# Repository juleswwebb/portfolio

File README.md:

# Jules Webb — Engineering Portfolio

A static engineering portfolio for **https://juleswwebb.github.io/portfolio/**.

The site includes an editorial homepage, four standalone project case studies,
an interactive subsystem viewer, project filters, image detail dialogs, responsive
navigation and social sharing metadata. It uses plain HTML, CSS and JavaScript,
with locally hosted images and no runtime dependencies, trackers or external fonts.

## Preview

```bash
python3 -m http.server 4173
```

Open http://localhost:4173. Run `python3 verify.py` to check local links, fragment
targets, images, headings and metadata. Run `node --check app.js` for JavaScript
syntax validation.

## Deploy

In this repository’s **Settings → Pages → Build and deployment**, select
**GitHub Actions** as the source. The workflow in `.github/workflows/pages.yml`
validates and deploys the public site files after a push to `main`. It can also
be run manually from the Actions tab.

Only the HTML pages, CSS, JavaScript, assets and crawler files are included in
the deployed artifact. The source does not contain the LinkedIn PDF, coursework
reports, firmware, engineering source repositories or private recordings.

## Update

- Edit `index.html` for the introduction, experience, contact links and project cards.
- Edit each project’s HTML for its case study and credits.
- Edit `styles.css` for the design; `app.js` controls progressive enhancements.
- Put optimised project images in `assets/`; update alt text and captions too.
- Update canonical URLs, `sitemap.xml`, `robots.txt`, the social-image URL and
  `404.html` if the repository name or hosting domain changes.

## Content provenance

Professional information and the LinkedIn URL were taken from the user-supplied
LinkedIn profile export dated 7 October 2026. No private analytics or unrelated
profile recommendations were used.

- **Line follower:** Group 13 project report, design figures and application images.
  Team members and reported results are credited in the case study.
- **RoboDev:** collaborative repository documentation and a 3D render made from
  its current KiCad signals board. Planned specifications are identified as such;
  the visualisation does not imply fabricated or validated hardware.
- **RoboCup:** project firmware/tooling documentation and an Arena View screenshot.
  Ongoing hardware validation and dead-reckoning limitations are stated.
- **Frame solver:** application documentation and generated analysis figures.
  Historical reference checks are described as documented development history.

Confirm specific individual contributions before changing the team descriptions
to first-person ownership claims. Update development status as projects progress.

## Interactive browser edition

Seven case studies now include the elevator PLC, CNC mechanical design and ENCE361 step counter. `structure-lab.html` runs a JavaScript port of the original Python direct-stiffness engine in a module worker. It supports axial trusses, Euler–Bernoulli / Timoshenko frames, end releases, rotated supports, nodal and member loads, drawing/editing, undo/redo, JSON sessions, force diagrams and worked matrix downloads. Internal units are SI; UI conversions are explicit. Deformation uses finite-element interpolation, and stress output is axial stress (bending and buckling checks are not included).

`node tests/fea-engine.test.mjs` checks analytical mechanics, stability failures, constrained-load reactions and frozen results generated from the original Python `frame_toolkit.Structure`. The Pages workflow runs these checks alongside the static-site verifier.

`design-library.html` uses a self-hosted Apache-licensed model-viewer (license included) to render actual GLB geometry. Models load on selection; rendered PCB views use optimized WebP previews and downloadable full PNGs. Camera presets, orbit/zoom, auto-rotation, studio background and view export are available. Download packs include actual available source CAD and renders. All original project workspaces remain untouched.

The shared Group 13 OneDrive folder contains files that are cloud placeholders and could not be opened during this export. Affected native archives are marked partial, omit unavailable files and contain `FILES-AWAITING-ONEDRIVE-SYNC.txt`. `assets/models/source-inventory.json` records inclusion status. Supplied STL/3MF exports provide mechanical browser geometry; SolidWorks source parts/assemblies remain native downloads. 3MF placements are print layouts, not reconstructed robot assemblies. Component-library STEP references are identified separately from custom PCB designs.

The elevator, CNC and step-counter web demos are labelled recreations/illustrations. They do not execute the physical controller firmware or claim measured hardware performance. Actual CNC and step-counter project photography is pending.

Motion uses native CSS, SVG and canvas, pauses expensive loops offscreen and honours reduced-motion preferences. No analytics or account/login is required. Locally saved structural models remain in the visitor's browser.

PCB GLB materials use the green default soldermask seen in the KiCad rendered previews. CAD geometry is retained; component materials are adjusted for readable browser lighting. Source STEP and KiCad exports remain available.

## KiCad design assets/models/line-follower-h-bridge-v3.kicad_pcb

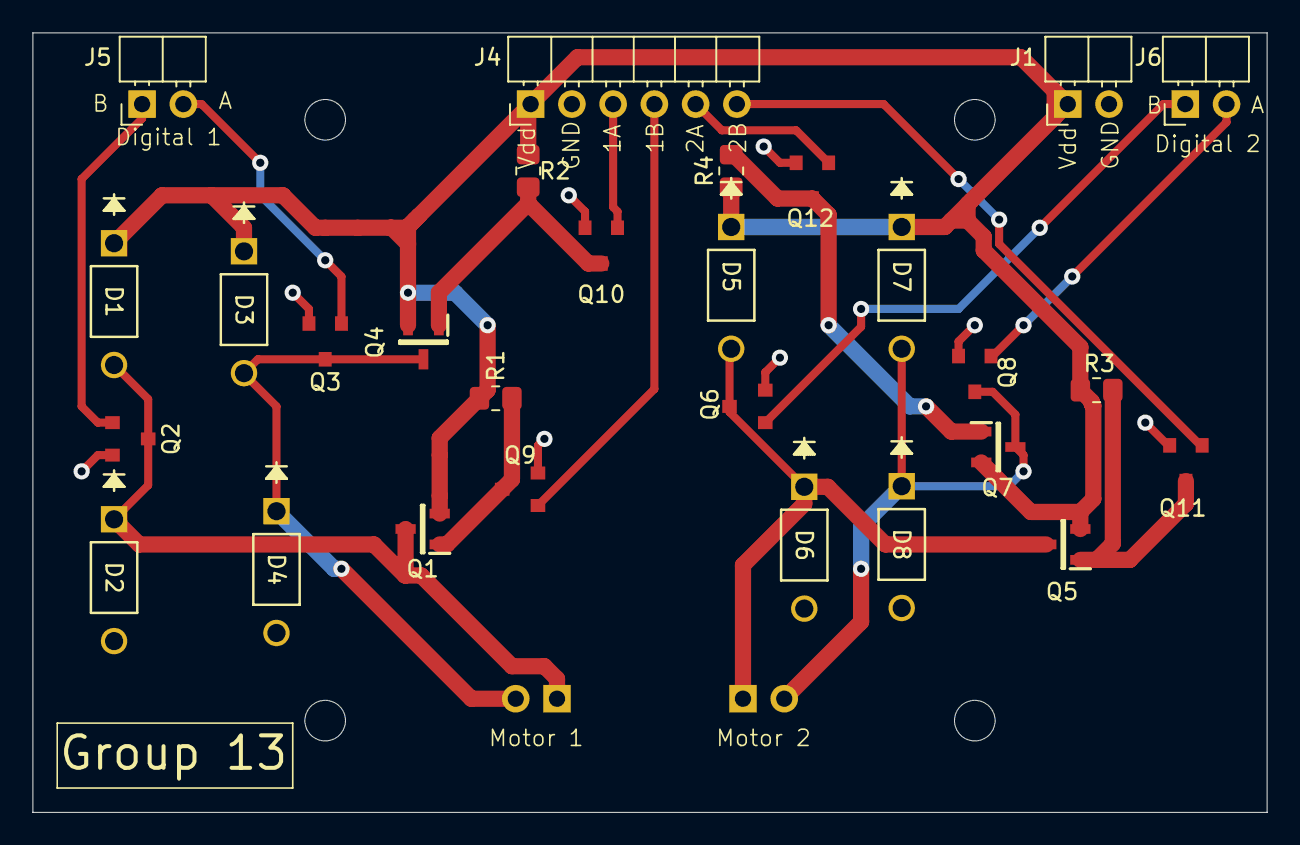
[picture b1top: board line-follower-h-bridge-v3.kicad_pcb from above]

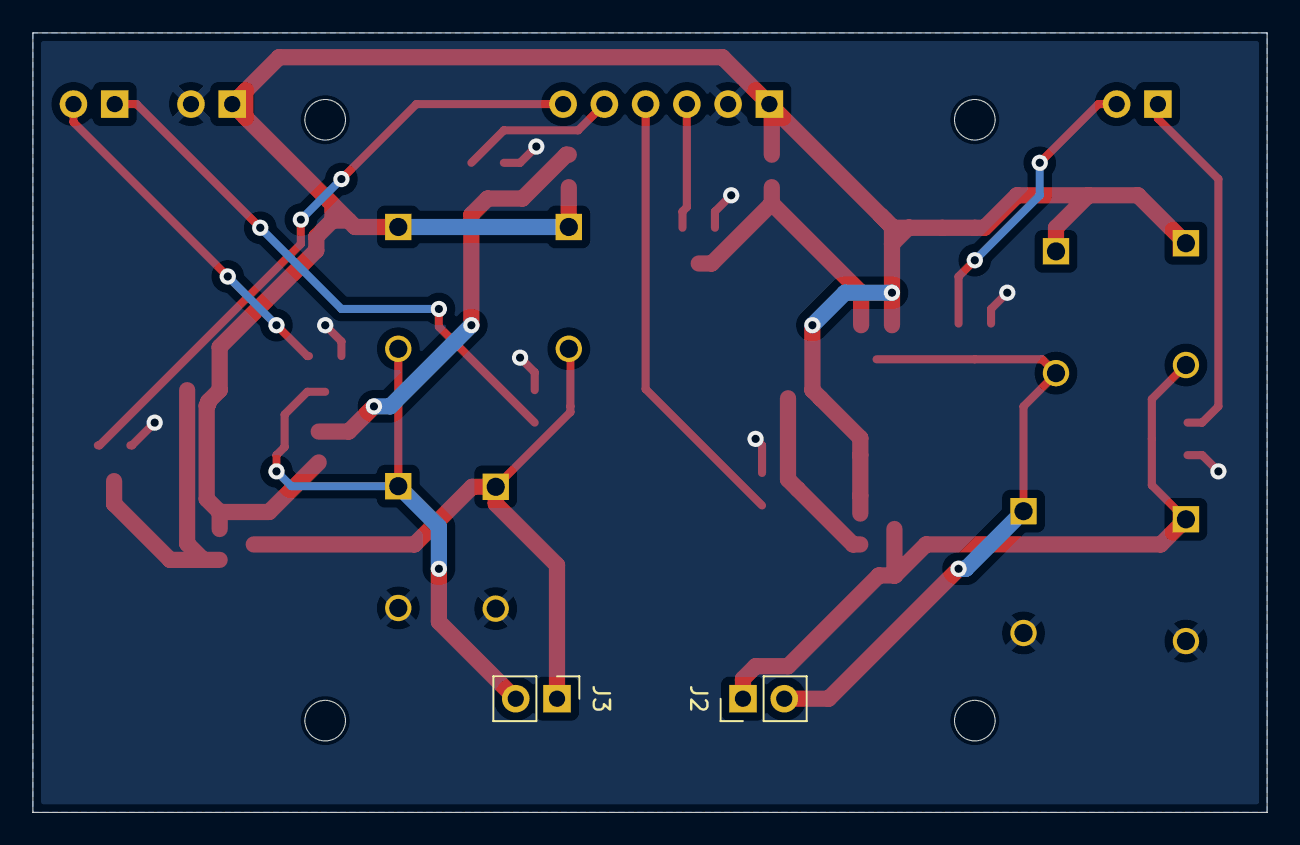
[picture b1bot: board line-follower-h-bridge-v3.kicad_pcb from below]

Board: 2 copper layers, 76.0 x 48.0 mm, 34 parts (2 on the bottom side), 18 nets.

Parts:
D1, D2, D3, D4, D5, D6, D7, D8: D; DO-41_DIO
H1, H2, H3, H4: MountingHole; MountingHole_2.5mm
J1: Battery; PinHeader_1x02_P2.54mm_Horizontal
J2: Motor 1; PinHeader_1x02_P2.54mm_Vertical
J3: Motor 2; PinHeader_1x02_P2.54mm_Vertical
J4: Conn_01x06; PinHeader_1x06_P2.54mm_Horizontal
J5, J6: Conn_01x02; PinHeader_1x02_P2.54mm_Horizontal
Q1, Q4, Q5, Q7: SI2333DDS-T1-GE3; SOT95P237X112-3N
Q2, Q3, Q6, Q8, Q9, Q10, Q11, Q12: BSR802NL6327HTSA1; TRANS_BC846B_215
R1, R2, R3, R4: 10k; R_0805_2012Metric_Pad1.20x1.40mm_HandSolder

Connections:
Dig1A: J5.2, Q3.1 (G)
Dig1B: J5.1, Q2.1 (G)
Dig2A: J6.2, Q8.1 (G)
Dig2B: J6.1, Q6.1 (G)
GND: D2.2 (A), D4.2 (A), D6.2 (A), D8.2 (A), J1.2, J4.2, Q2.2 (S), Q3.2 (S), Q6.2 (S), Q8.2 (S), Q9.2 (S), Q10.2 (S), Q11.2 (S), Q12.2 (S)
unnamed: D1.2 (A), D2.1 (K), J2.1, Q1.3, Q2.3 (D)
unnamed: D3.2 (A), D4.1 (K), J2.2, Q3.3 (D), Q4.3
unnamed: D5.2 (A), D6.1 (K), J3.1, Q5.3, Q6.3 (D)
unnamed: D7.2 (A), D8.1 (K), J3.2, Q7.3, Q8.3 (D)
unnamed: Q1.1, Q9.3 (D), R1.2
unnamed: Q4.1, Q10.3 (D), R2.2
unnamed: Q5.1, Q11.3 (D), R3.2
unnamed: Q7.1, Q12.3 (D), R4.2
PWM1A: J4.3, Q10.1 (G)
PWM1B: J4.4, Q9.1 (G)
PWM2A: J4.5, Q12.1 (G)
PWM2B: J4.6, Q11.1 (G)
Vdd: D1.1 (K), D3.1 (K), D5.1 (K), D7.1 (K), J1.1, J4.1, Q1.2, Q4.2, Q5.2, Q7.2, R1.1, R2.1, R3.1, R4.1

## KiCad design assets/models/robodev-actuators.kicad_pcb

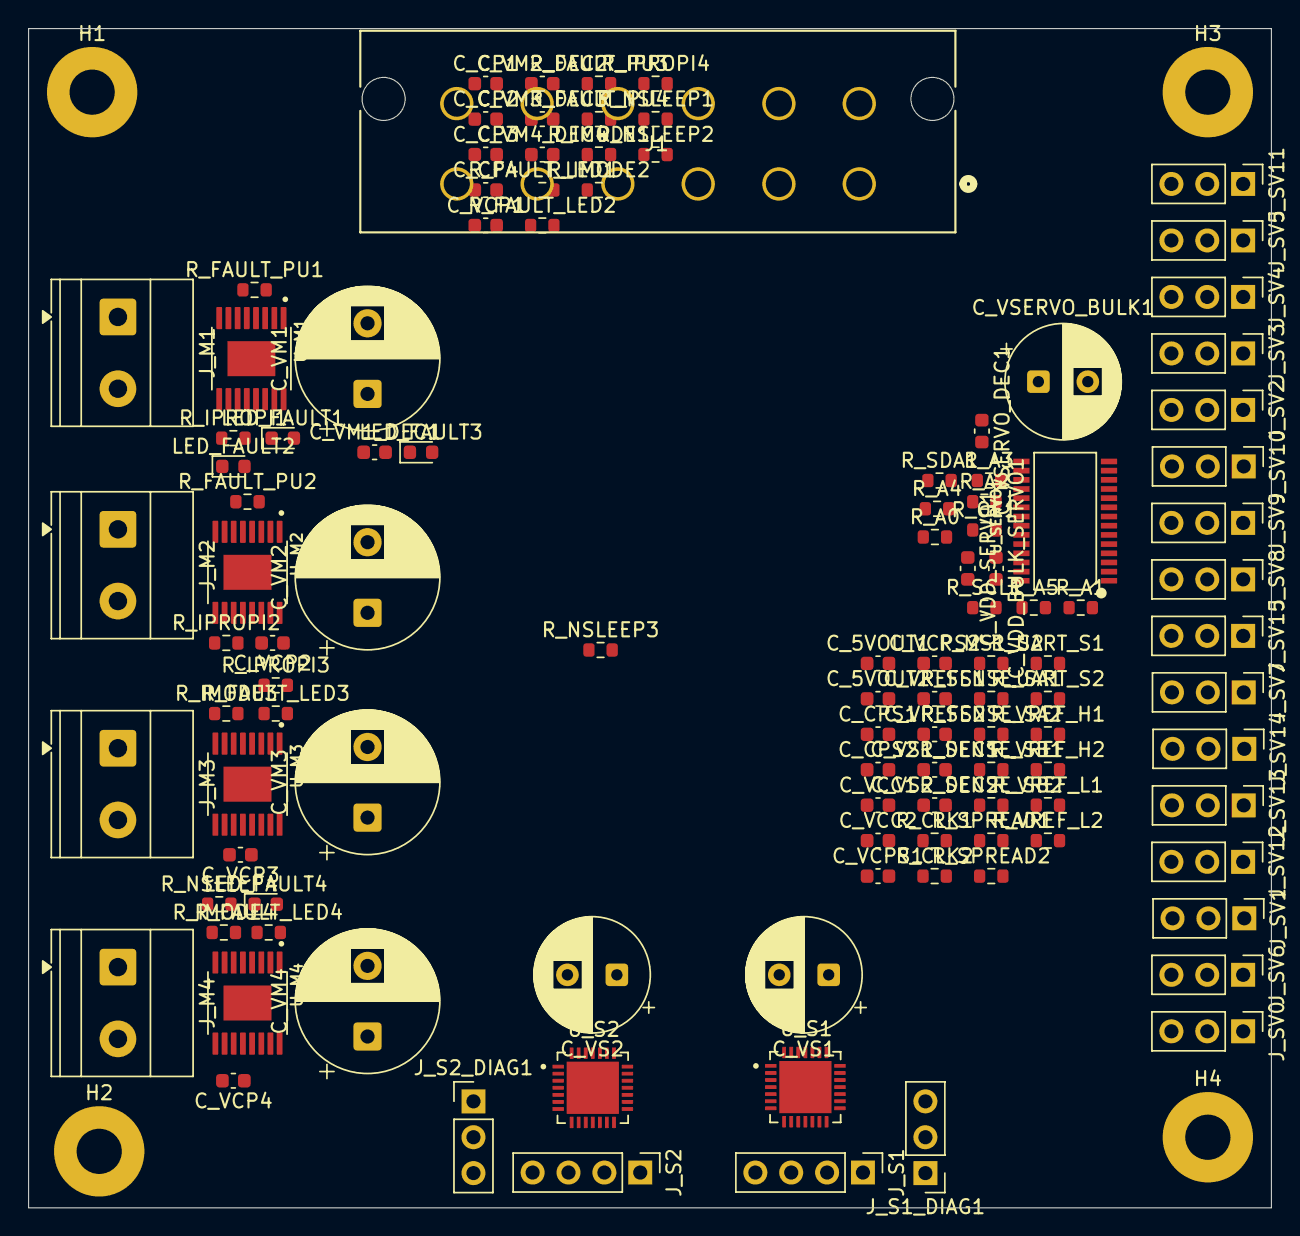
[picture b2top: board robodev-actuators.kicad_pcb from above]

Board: 4 copper layers, 88.0 x 83.5 mm, 118 parts (0 on the bottom side), 113 nets, no tracks yet.

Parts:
C_5VOUT1, C_5VOUT2: 4.7 µF 10V X5R; C_0603_1608Metric
C_CP1: 22nF 50V X7R; C_0603_1608Metric
C_CP2, C_CP3, C_CP4: 22 nF 50V X7R; C_0603_1608Metric
C_CPS1, C_CPS2: 100 nF 50V X7R; C_0603_1608Metric
C_VCC1, C_VCC2: 100 nF 10V X7R; C_0603_1608Metric
C_VCP1, C_VCP2, C_VCP3, C_VCP4: 100 nF 50V X7R; C_0603_1608Metric
C_VCPS1, C_VCPS2: 100 nF 50V X7R; C_0603_1608Metric
C_VDD_BULK_SERVO1: 10 µF 10V X5R; C_0603_1608Metric
C_VDD_SERVO1: 100 nF 10V X7R; C_0603_1608Metric
C_VM1, C_VM2, C_VM3, C_VM4: 470 µF 50V electrolytic; CP_Radial_D10.0mm_P5.00mm
C_VM1_DEC1, C_VM2_DEC2, C_VM3_DEC3, C_VM4_DEC4: 100 nF 50V X7R; C_0603_1608Metric
C_VREFS1, C_VREFS2: 100 nF 10V X7R; C_0603_1608Metric
C_VS1, C_VS2: 100 µF 50V electrolytic; CP_Radial_D8.0mm_P3.50mm
C_VS1_DEC1, C_VS2_DEC2: 100 nF 50V X7R; C_0603_1608Metric
C_VSERVO_BULK1: 220 µF 25V electrolytic; CP_Radial_D8.0mm_P3.50mm
C_VSERVO_DEC1: 100 nF 50V X7R; C_0603_1608Metric
H1, H2, H3, H4: MountingHole_Pad; MountingHole_3.2mm_M3_Pad
J1: 768290012; CONN_SD-76829-0100_12_MOL
J_M1, J_M2, J_M3, J_M4: Conn_01x02; TerminalBlock_Phoenix_MKDS-1,5-2-5.08_1x02_P5.08mm_Horizont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
J_S1, J_S2: Stepper 4-pin 2.54mm; PinHeader_1x04_P2.54mm_Vertical
J_S1_DIAG1: Stepper 1 DIAG/INDEX; PinHeader_1x03_P2.54mm_Vertical
J_S2_DIAG1: Stepper 2 DIAG/INDEX; PinHeader_1x03_P2.54mm_Vertical
J_SV0, J_SV1, J_SV2, J_SV3, J_SV4, J_SV5, J_SV6, J_SV7, J_SV8, J_SV9, J_SV10, J_SV11, J_SV12, J_SV13, J_SV14, J_SV15: Conn_01x03; PinHeader_1x03_P2.54mm_Vertical
LED_FAULT1, LED_FAULT2, LED_FAULT3, LED_FAULT4: LTST-C190KRKT Red; LED_0603_1608Metric
R_A0, R_A1, R_A2, R_A3, R_A4, R_A5: 100 kΩ 1% 0603; R_0603_1608Metric
R_CLK1, R_CLK2: 100 kΩ 1% 0603; R_0603_1608Metric
R_FAULT_LED1, R_FAULT_LED2, R_FAULT_LED3, R_FAULT_LED4: 1 kΩ 1% 0603; R_0603_1608Metric
R_FAULT_PU1, R_FAULT_PU2, R_FAULT_PU3, R_FAULT_PU4: 10 kΩ 1% 0603; R_0603_1608Metric
R_IMODE1, R_IMODE2, R_IMODE3, R_IMODE4: 20 kΩ 1% 0603; R_0603_1608Metric
R_IPROPI1, R_IPROPI2, R_IPROPI3, R_IPROPI4: 1 kΩ 1% 0603; R_0603_1608Metric
R_MS1_S2: 10 kΩ 1% 0603; R_0603_1608Metric
R_NSLEEP1, R_NSLEEP2, R_NSLEEP3, R_NSLEEP4: 100 kΩ 1% 0603; R_0603_1608Metric
R_OE1: 100 kΩ 1% 0603; R_0603_1608Metric
R_SCL1: 4.7 kΩ 1% 0603; R_0603_1608Metric
R_SDA1: 4.7 kΩ 1% 0603; R_0603_1608Metric
R_SENSE_SA1, R_SENSE_SA2: 100 mΩ 1% 0603; R_0603_1608Metric
R_SENSE_SB1, R_SENSE_SB2: 100 mΩ 1% 0603; R_0603_1608Metric
R_SPREAD1, R_SPREAD2: 100 kΩ 1% 0603; R_0603_1608Metric
R_UART_S1, R_UART_S2: 1 kΩ 1% 0603; R_0603_1608Metric
R_VREF_H1, R_VREF_H2: 10 kΩ 1% 0603; R_0603_1608Metric
R_VREF_L1, R_VREF_L2: 27 kΩ 1% 0603; R_0603_1608Metric
U_M1, U_M2, U_M3, U_M4: DRV8874PWPR; SOP65P640X120-17N
U_S1, U_S2: TMC2209-LA-T; QFN50P500X500X90-29N
U_SERVO1: PCA9685PW; TSSOP28-0.65-9.7X4.4MM

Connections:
+3V3: C_VCC1.2, C_VCC2.2, C_VDD_BULK_SERVO1.2, C_VDD_SERVO1.2, R_FAULT_PU1.1, R_FAULT_PU2.1, R_FAULT_PU3.1, R_FAULT_PU4.1, R_MS1_S2.1, R_NSLEEP1.1, R_NSLEEP2.1, R_NSLEEP3.1, R_NSLEEP4.1, R_SCL1.1, R_SDA1.1, R_VREF_H1.1, R_VREF_H2.1, U_M1.5 (VREF), U_M2.5 (VREF), U_M3.5 (VREF), U_M4.5 (VREF), U_S1.15 (VCC_IO), U_S2.15 (VCC_IO), U_SERVO1.28 (VDD)
/MGND: J1.7, J1.8
/SERVOGND: J1.11, J1.12
/STEPGND: J1.9, J1.10
/V_MOT: J1.3, J1.4
/V_SERVO: J1.1, J1.2
/V_STEP: J1.5, J1.6
/motor_dc/IPROPI_M1: R_IPROPI1.1, U_M1.6 (IPROPI)
/motor_dc/IPROPI_M2: R_IPROPI2.1, U_M2.6 (IPROPI)
/motor_dc/IPROPI_M3: R_IPROPI3.1, U_M3.6 (IPROPI)
/motor_dc/IPROPI_M4: R_IPROPI4.1, U_M4.6 (IPROPI)
/motor_dc/VMOT: C_VCP1.2, C_VCP2.2, C_VCP3.2, C_VCP4.2, C_VM1.1, C_VM1_DEC1.1, C_VM2.1, C_VM2_DEC2.1, C_VM3.1, C_VM3_DEC3.1, C_VM4.1, C_VM4_DEC4.1, U_M1.11 (VM), U_M2.11 (VM), U_M3.11 (VM), U_M4.11 (VM)
/motor_servo/I2C_SCL: R_SCL1.2, U_SERVO1.26 (SCL)
/motor_servo/I2C_SDA: R_SDA1.2, U_SERVO1.27 (SDA)
/motor_servo/SV_PWM0: J_SV0.3, U_SERVO1.6 (LED0)
/motor_servo/SV_PWM1: J_SV1.3, U_SERVO1.7 (LED1)
/motor_servo/SV_PWM2: J_SV2.3, U_SERVO1.8 (LED2)
/motor_servo/SV_PWM3: J_SV3.3, U_SERVO1.9 (LED3)
/motor_servo/SV_PWM4: J_SV4.3, U_SERVO1.10 (LED4)
/motor_servo/SV_PWM5: J_SV5.3, U_SERVO1.11 (LED5)
/motor_servo/SV_PWM6: J_SV6.3, U_SERVO1.12 (LED6)
/motor_servo/SV_PWM7: J_SV7.3, U_SERVO1.13 (LED7)
/motor_servo/SV_PWM8: J_SV8.3, U_SERVO1.15 (LED8)
/motor_servo/SV_PWM9: J_SV9.3, U_SERVO1.16 (LED9)
/motor_servo/SV_PWM10: J_SV10.3, U_SERVO1.17 (LED10)
/motor_servo/SV_PWM11: J_SV11.3, U_SERVO1.18 (LED11)
/motor_servo/SV_PWM12: J_SV12.3, U_SERVO1.19 (LED12)
/motor_servo/SV_PWM13: J_SV13.3, U_SERVO1.20 (LED13)
/motor_servo/SV_PWM14: J_SV14.3, U_SERVO1.21 (LED14)
/motor_servo/SV_PWM15: J_SV15.3, U_SERVO1.22 (LED15)
/motor_stepper/S1_VREF: C_VREFS1.1, R_VREF_H1.2, R_VREF_L1.1, U_S1.17 (VREF)
/motor_stepper/S2_VREF: C_VREFS2.1, R_VREF_H2.2, R_VREF_L2.1, U_S2.17 (VREF)
/motor_stepper/TMC_UART: R_UART_S1.1, R_UART_S2.1
GND: C_5VOUT1.2, C_5VOUT2.2, C_VCC1.1, C_VCC2.1, C_VDD_BULK_SERVO1.1, C_VDD_SERVO1.1, C_VM1.2, C_VM1_DEC1.2, C_VM2.2, C_VM2_DEC2.2, C_VM3.2, C_VM3_DEC3.2, C_VM4.2, C_VM4_DEC4.2, C_VREFS1.2, C_VREFS2.2, H1.1, H2.1, H3.1, H4.1, J_S1_DIAG1.1, J_S2_DIAG1.1, LED_FAULT1.1 (K), LED_FAULT2.1 (K), LED_FAULT3.1 (K), LED_FAULT4.1 (K), R_A0.1, R_A1.1, R_A2.1, R_A3.1, R_A4.1, R_A5.1, R_CLK1.1, R_CLK2.1, R_IMODE1.1, R_IMODE2.1, R_IMODE3.1, R_IMODE4.1, R_IPROPI1.2, R_IPROPI2.2, R_IPROPI3.2, R_IPROPI4.2, R_OE1.1, R_SPREAD1.1, R_SPREAD2.1, R_VREF_L1.2, R_VREF_L2.2, U_M1.16 (PMODE), U_M2.16 (PMODE), U_M3.16 (PMODE), U_M4.16 (PMODE), U_S1.9 (MS1_AD0), U_S1.10 (MS2_AD1), U_S2.10 (MS2_AD1), U_SERVO1.14 (VSS), U_SERVO1.25 (EXTCLK)
MGND: U_M1.9 (PGND), U_M1.15 (GND), U_M2.9 (PGND), U_M2.15 (GND), U_M3.9 (PGND), U_M3.15 (GND), U_M4.9 (PGND), U_M4.15 (GND)
unnamed: J_M1.1, U_M1.8 (OUT1)
unnamed: J_M1.2, U_M1.10 (OUT2)
unnamed: J_M2.1, U_M2.8 (OUT1)
unnamed: J_M2.2, U_M2.10 (OUT2)
unnamed: J_M3.1, U_M3.8 (OUT1)
unnamed: J_M3.2, U_M3.10 (OUT2)
unnamed: J_M4.1, U_M4.8 (OUT1)
unnamed: J_M4.2, U_M4.10 (OUT2)
unnamed: J_S1.1, U_S1.24 (OA1)
unnamed: J_S1.2, U_S1.21 (OA2)
unnamed: J_S1.3, U_S1.26 (OB1)
unnamed: J_S1.4, U_S1.1 (OB2)
unnamed: J_S1_DIAG1.2, U_S1.11 (DIAG)
unnamed: J_S1_DIAG1.3, U_S1.12 (INDEX)
unnamed: J_S2.1, U_S2.24 (OA1)
unnamed: J_S2.2, U_S2.21 (OA2)
unnamed: J_S2.3, U_S2.26 (OB1)
unnamed: J_S2.4, U_S2.1 (OB2)
unnamed: J_S2_DIAG1.2, U_S2.11 (DIAG)
unnamed: J_S2_DIAG1.3, U_S2.12 (INDEX)
unnamed: LED_FAULT1.2 (A), R_FAULT_LED1.2
unnamed: LED_FAULT2.2 (A), R_FAULT_LED2.2
unnamed: LED_FAULT3.2 (A), R_FAULT_LED3.2
unnamed: LED_FAULT4.2 (A), R_FAULT_LED4.2
unnamed: C_CP1.1, U_M1.13 (CPH)
unnamed: C_CP1.2, U_M1.14 (CPL)
unnamed: R_IMODE1.2, U_M1.7 (IMODE)
unnamed: R_FAULT_LED1.1, R_FAULT_PU1.2, U_M1.4 (NFAULT)
unnamed: R_NSLEEP1.2, U_M1.3 (NSLEEP)
unnamed: C_VCP1.1, U_M1.12 (VCP)
unnamed: C_CP2.1, U_M2.13 (CPH)
unnamed: C_CP2.2, U_M2.14 (CPL)
unnamed: R_IMODE2.2, U_M2.7 (IMODE)
unnamed: R_FAULT_LED2.1, R_FAULT_PU2.2, U_M2.4 (NFAULT)
unnamed: R_NSLEEP2.2, U_M2.3 (NSLEEP)
unnamed: C_VCP2.1, U_M2.12 (VCP)
unnamed: C_CP3.1, U_M3.13 (CPH)
unnamed: C_CP3.2, U_M3.14 (CPL)
unnamed: R_IMODE3.2, U_M3.7 (IMODE)
unnamed: R_FAULT_LED3.1, R_FAULT_PU3.2, U_M3.4 (NFAULT)
unnamed: R_NSLEEP3.2, U_M3.3 (NSLEEP)
unnamed: C_VCP3.1, U_M3.12 (VCP)
unnamed: C_CP4.1, U_M4.13 (CPH)
unnamed: C_CP4.2, U_M4.14 (CPL)
unnamed: R_IMODE4.2, U_M4.7 (IMODE)
unnamed: R_FAULT_LED4.1, R_FAULT_PU4.2, U_M4.4 (NFAULT)
unnamed: R_NSLEEP4.2, U_M4.3 (NSLEEP)
unnamed: C_VCP4.1, U_M4.12 (VCP)
unnamed: C_5VOUT1.1, U_S1.8 (5VOUT)
unnamed: R_SENSE_SA1.1, U_S1.23 (BRA)
unnamed: R_SENSE_SB1.1, U_S1.27 (BRB)
unnamed: R_CLK1.2, U_S1.13 (CLK)
unnamed: C_CPS1.1, U_S1.5 (CPI)
unnamed: C_CPS1.2, U_S1.4 (CPO)
unnamed: R_SPREAD1.2, U_S1.7 (SPREAD)
unnamed: C_VCPS1.1, U_S1.6 (VCP)
unnamed: R_UART_S1.2, U_S1.14 (~PD_UART)
unnamed: C_5VOUT2.1, U_S2.8 (5VOUT)
unnamed: R_SENSE_SA2.1, U_S2.23 (BRA)
unnamed: R_SENSE_SB2.1, U_S2.27 (BRB)
unnamed: R_CLK2.2, U_S2.13 (CLK)
unnamed: C_CPS2.1, U_S2.5 (CPI)
unnamed: C_CPS2.2, U_S2.4 (CPO)
unnamed: R_MS1_S2.2, U_S2.9 (MS1_AD0)
unnamed: R_SPREAD2.2, U_S2.7 (SPREAD)
unnamed: C_VCPS2.1, U_S2.6 (VCP)
unnamed: R_UART_S2.2, U_S2.14 (~PD_UART)
unnamed: R_A0.2, U_SERVO1.1 (A0)
unnamed: R_A1.2, U_SERVO1.2 (A1)
unnamed: R_A2.2, U_SERVO1.3 (A2)
unnamed: R_A3.2, U_SERVO1.4 (A3)
unnamed: R_A4.2, U_SERVO1.5 (A4)
unnamed: R_A5.2, U_SERVO1.24 (A5)
unnamed: R_OE1.2, U_SERVO1.23 (~OE)
SERVOGND: C_VSERVO_BULK1.2, C_VSERVO_DEC1.2, J_SV0.1, J_SV1.1, J_SV2.1, J_SV3.1, J_SV4.1, J_SV5.1, J_SV6.1, J_SV7.1, J_SV8.1, J_SV9.1, J_SV10.1, J_SV11.1, J_SV12.1, J_SV13.1, J_SV14.1, J_SV15.1
STEPGND: C_VCPS1.2, C_VCPS2.2, C_VS1.2, C_VS1_DEC1.1, C_VS2.2, C_VS2_DEC2.1, R_SENSE_SA1.2, R_SENSE_SA2.2, R_SENSE_SB1.2, R_SENSE_SB2.2, U_S1.3 (GND), U_S2.3 (GND)
VS: C_VS1.1, C_VS1_DEC1.2, C_VS2.1, C_VS2_DEC2.2, U_S1.22 (VS), U_S1.28 (VS), U_S2.22 (VS), U_S2.28 (VS)
VSERVO: C_VSERVO_BULK1.1, C_VSERVO_DEC1.1, J_SV0.2, J_SV1.2, J_SV2.2, J_SV3.2, J_SV4.2, J_SV5.2, J_SV6.2, J_SV7.2, J_SV8.2, J_SV9.2, J_SV10.2, J_SV11.2, J_SV12.2, J_SV13.2, J_SV14.2, J_SV15.2

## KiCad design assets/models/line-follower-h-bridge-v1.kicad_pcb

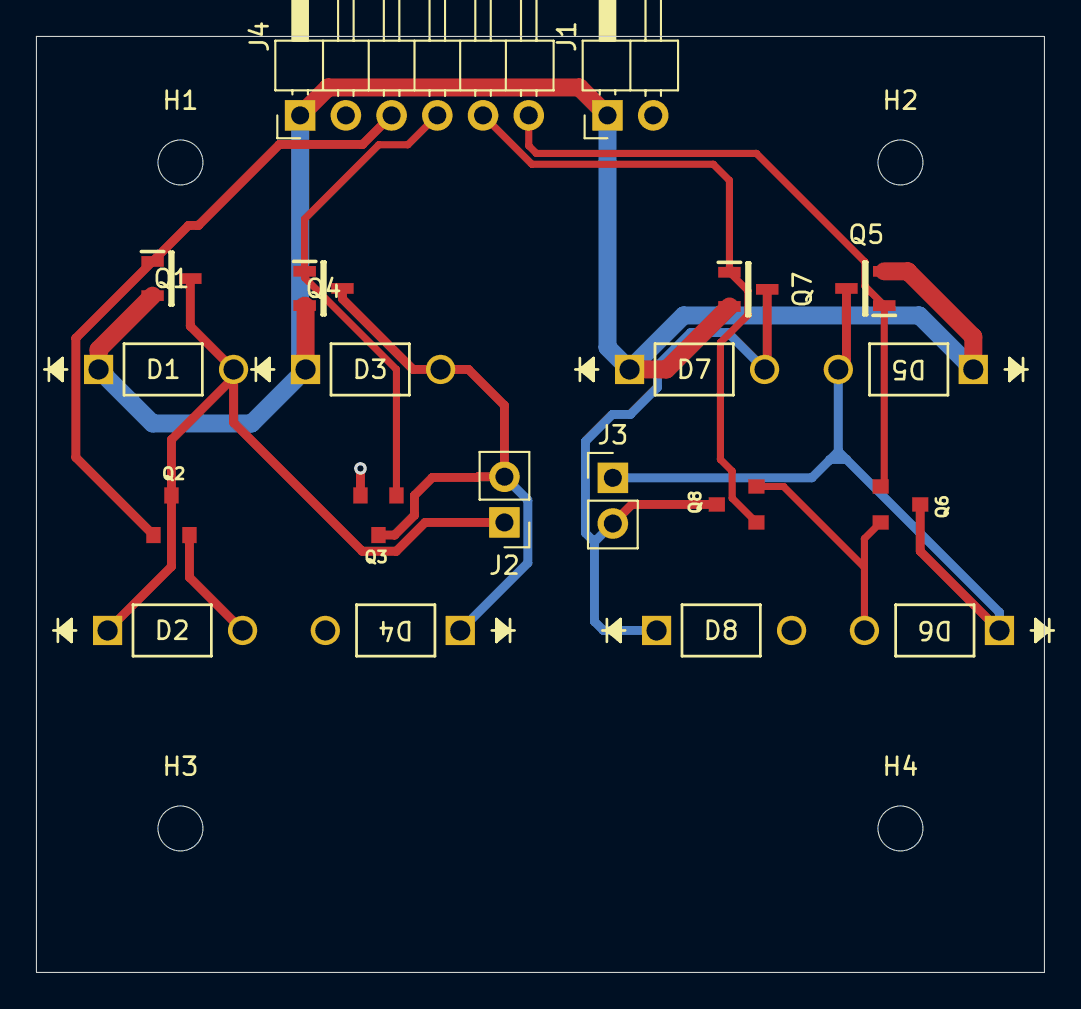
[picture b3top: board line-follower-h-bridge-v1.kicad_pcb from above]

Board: 2 copper layers, 56.0 x 52.0 mm, 24 parts (0 on the bottom side), 10 nets.

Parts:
D1, D2, D3, D4, D5, D6, D7, D8: D; DO-41_DIO
H1, H2, H3, H4: MountingHole; MountingHole_2.5mm
J1: Battery; PinHeader_1x02_P2.54mm_Horizontal
J2: Motor 1; PinHeader_1x02_P2.54mm_Vertical
J3: Motor 2; PinHeader_1x02_P2.54mm_Vertical
J4: Data Header; PinHeader_1x06_P2.54mm_Horizontal
Q1, Q4, Q5, Q7: SI2333DDS-T1-GE3; SOT95P237X112-3N
Q2, Q3, Q6, Q8: BSR802NL6327HTSA1; TRANS_BC846B_215

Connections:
GND: D2.2 (A), D4.2 (A), D6.2 (A), D8.2 (A), J1.2, J4.2, Q2.2 (S), Q3.2 (S), Q6.2 (S), Q8.2 (S)
unnamed: D1.2 (A), D2.1 (K), J2.1, Q1.3, Q2.3 (D)
unnamed: D3.2 (A), D4.1 (K), J2.2, Q3.3 (D), Q4.3
unnamed: D5.2 (A), D6.1 (K), J3.1, Q5.3, Q6.3 (D)
unnamed: D7.2 (A), D8.1 (K), J3.2, Q7.3, Q8.3 (D)
PWM1A: J4.4, Q3.1 (G), Q4.1
PWM1B: J4.3, Q1.1, Q2.1 (G)
PWM2A: J4.5, Q7.1, Q8.1 (G)
PWM2B: J4.6, Q5.1, Q6.1 (G)
Vdd: D1.1 (K), D3.1 (K), D5.1 (K), D7.1 (K), J1.1, J4.1, Q1.2, Q4.2, Q5.2, Q7.2

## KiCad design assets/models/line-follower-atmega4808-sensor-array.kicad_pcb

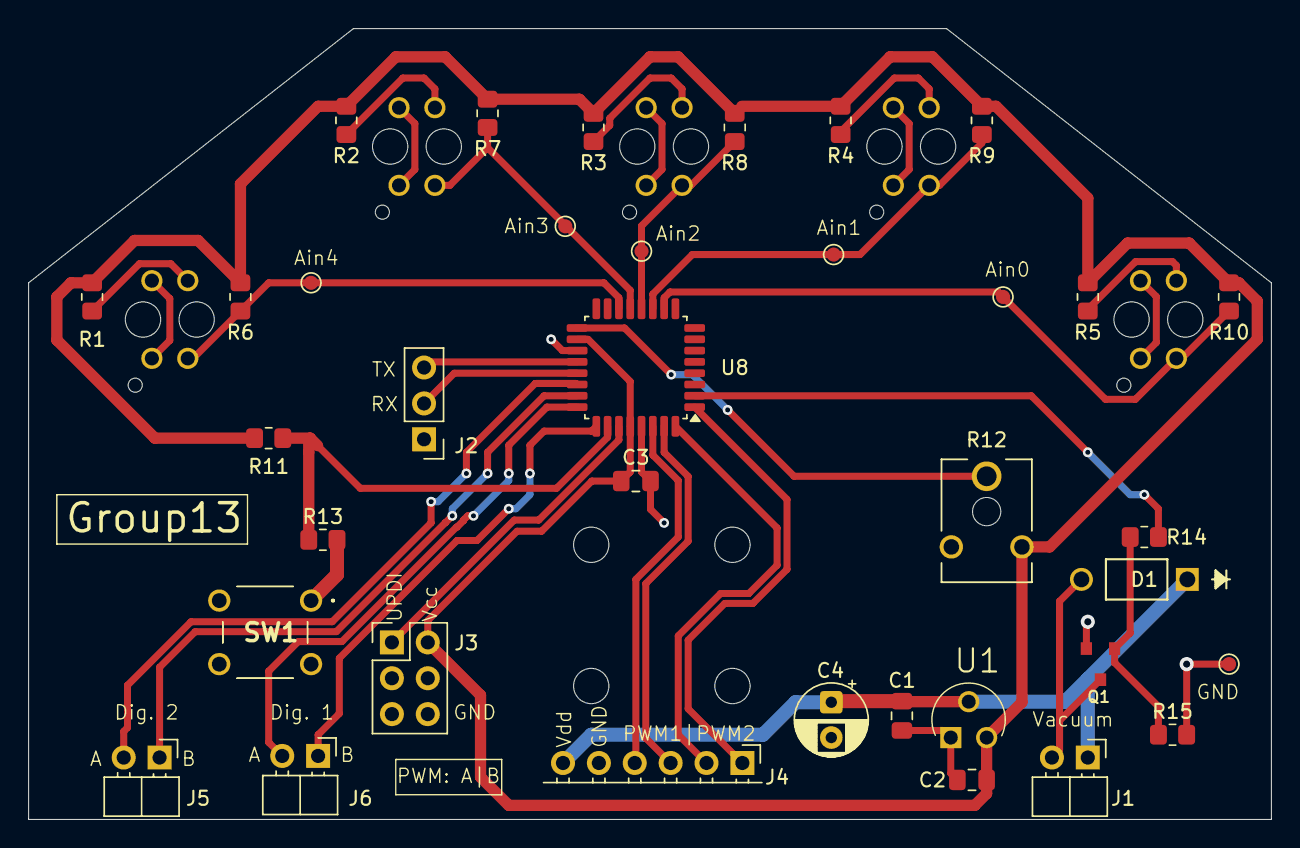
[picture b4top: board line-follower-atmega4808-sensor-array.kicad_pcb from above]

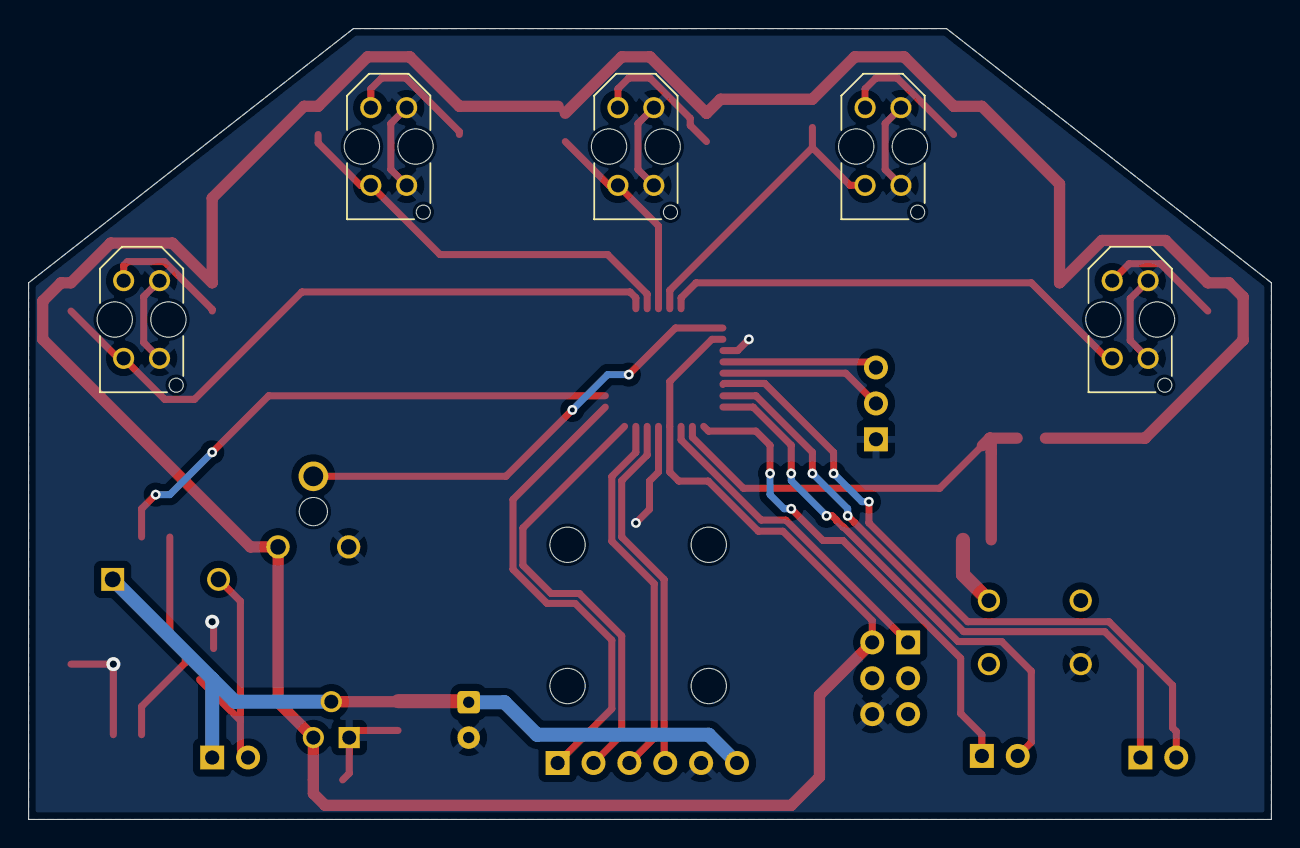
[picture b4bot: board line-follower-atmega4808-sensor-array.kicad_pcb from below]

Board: 2 copper layers, 88.0 x 56.0 mm, 45 parts (5 on the bottom side), 30 nets.

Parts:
C1, C2: 1u; C_0805_2012Metric_Pad1.18x1.45mm_HandSolder
C3: 10u; C_0805_2012Metric_Pad1.18x1.45mm_HandSolder
C4: 10u; CP_Radial_D5.0mm_P2.50mm
D1: D; DO-41_DIO
H1, H2, H3, H4: MountingHole; MountingHole_2.5mm
J1: Vacuum; PinHeader_1x02_P2.54mm_Horizontal
J2: Debugging; PinHeader_1x03_P2.54mm_Vertical
J3: UPDI Programmer; PinHeader_2x03_P2.54mm_Vertical
J4: PWM Header; PinHeader_1x06_P2.54mm_Horizontal
J5: Digital 2; PinHeader_1x02_P2.54mm_Horizontal
J6: Digital 1; PinHeader_1x02_P2.54mm_Horizontal
Q1: BSR802NL6327HTSA1; TRANS_BC846B_215
R1, R2, R3, R4, R5: 470; R_0805_2012Metric_Pad1.20x1.40mm_HandSolder
R6, R7, R8, R9, R10: 100k; R_0805_2012Metric_Pad1.20x1.40mm_HandSolder
R11, R15: 10k; R_0805_2012Metric_Pad1.20x1.40mm_HandSolder
R12: N6-L50T0C-103; TRIM_N6-L50T0C-103
R13: 330; R_0805_2012Metric_Pad1.20x1.40mm_HandSolder
R14: 220; R_0805_2012Metric_Pad1.20x1.40mm_HandSolder
SW1: SW_Push_Open; MJTP1230
TP1, TP2, TP3, TP4, TP5, TP6: TestPoint; TestPoint_Pad_D1.0mm
U1: MCP1700-3302E_TO; TO127P254X495-3
U3, U4, U5, U6, U7: TCRT5000; OPTO_TCRT5000
U8: ATmega4808-A; TQFP-32_7x7mm_P0.8mm

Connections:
Dig1A: J6.2, U8.24 (PF4)
Dig1B: J6.1, U8.25 (PF5)
Dig2A: J5.2, U8.22 (PF2)
Dig2B: J5.1, U8.23 (PF3)
GND: C1.2, C2.2, C3.2, C4.2, J2.1, J3.6, J4.5, Q1.2 (S), R12.A, R15.2, SW1.3 (B), TP6.1, U1.1 (GND), U3.CATH, U3.E, U4.CATH, U4.E, U5.CATH, U5.E, U6.CATH, U6.E, U7.CATH, U7.E, U8.19 (GND), U8.29 (GND)
unnamed: D1.2 (A), J1.2, Q1.3 (D)
unnamed: J2.2, U8.21 (PF1/TOSC2)
unnamed: J2.3, U8.20 (PF0/TOSC1)
unnamed: Q1.1 (G), R14.2, R15.1
unnamed: R1.2, U3.A
unnamed: R2.2, U4.A
unnamed: R3.2, U5.A
unnamed: R4.2, U6.A
unnamed: R5.2, U7.A
unnamed: R13.2, SW1.1 (A)
unnamed: R12.S, U8.17 (PD7)
unnamed: R11.2, R13.1, U8.26 (PF6/~RESET)
PWM1A: J4.4, U8.30 (EXTCLK/PA0)
PWM1B: J4.3, U8.31 (PA1)
PWM2A: J4.2, U8.32 (PA2)
PWM2B: J4.1, U8.1 (PA3)
Sensor1: R6.2, TP5.1, U3.COLL, U8.14 (PD4)
Sensor2: R7.2, TP4.1, U4.COLL, U8.13 (PD3)
Sensor3: R8.2, TP3.1, U5.COLL, U8.12 (PD2)
Sensor4: R9.2, TP2.1, U6.COLL, U8.11 (PD1)
Sensor5: R10.2, TP1.1, U7.COLL, U8.10 (PD0)
UPDI: J3.1, U8.27 (UPDI)
VacuumPWM: R14.1, U8.2 (PA4)
Vcc: C2.1, C3.1, J3.2, R1.1, R2.1, R3.1, R4.1, R5.1, R6.1, R7.1, R8.1, R9.1, R10.1, R11.1, R12.E, U1.3 (VOUT), U8.18 (AVDD), U8.28 (VDD)
Vdd: C1.1, C4.1, D1.1 (K), J1.1, J4.6, U1.2 (VIN)

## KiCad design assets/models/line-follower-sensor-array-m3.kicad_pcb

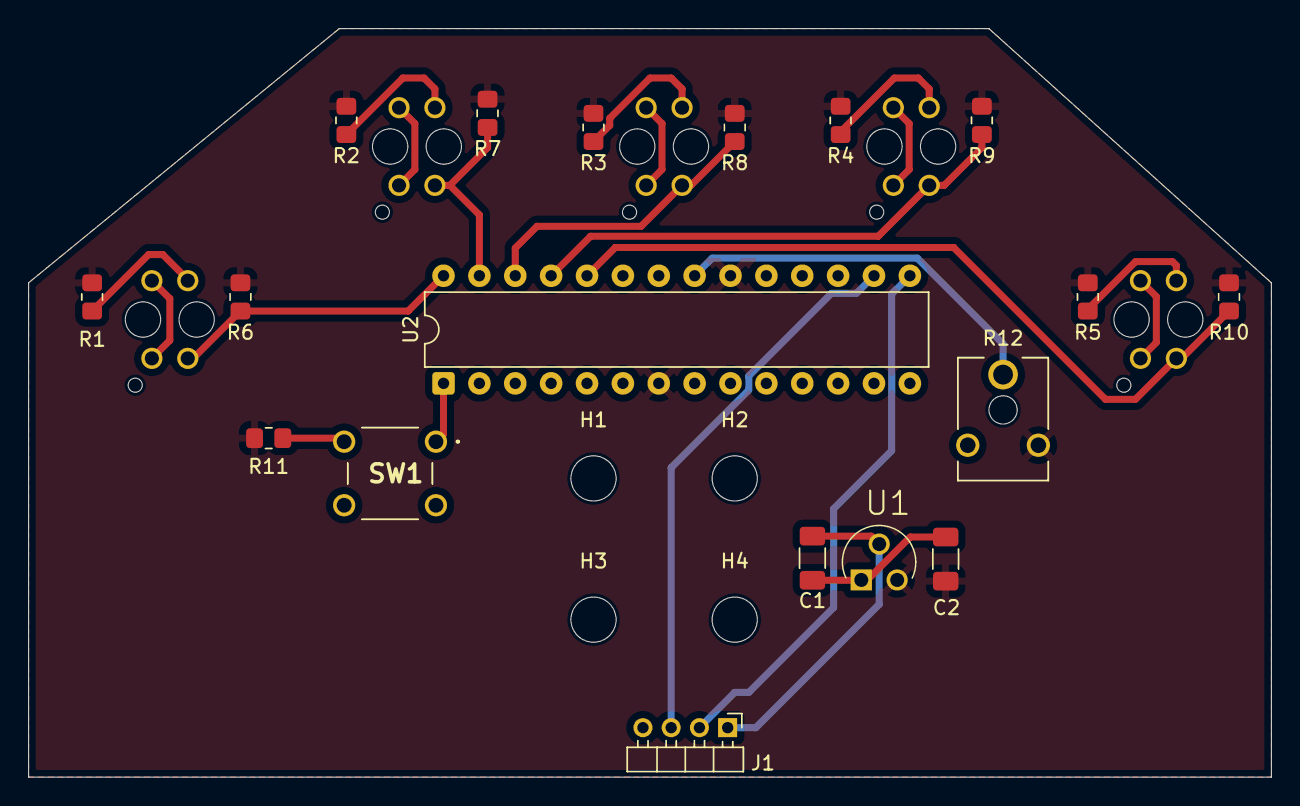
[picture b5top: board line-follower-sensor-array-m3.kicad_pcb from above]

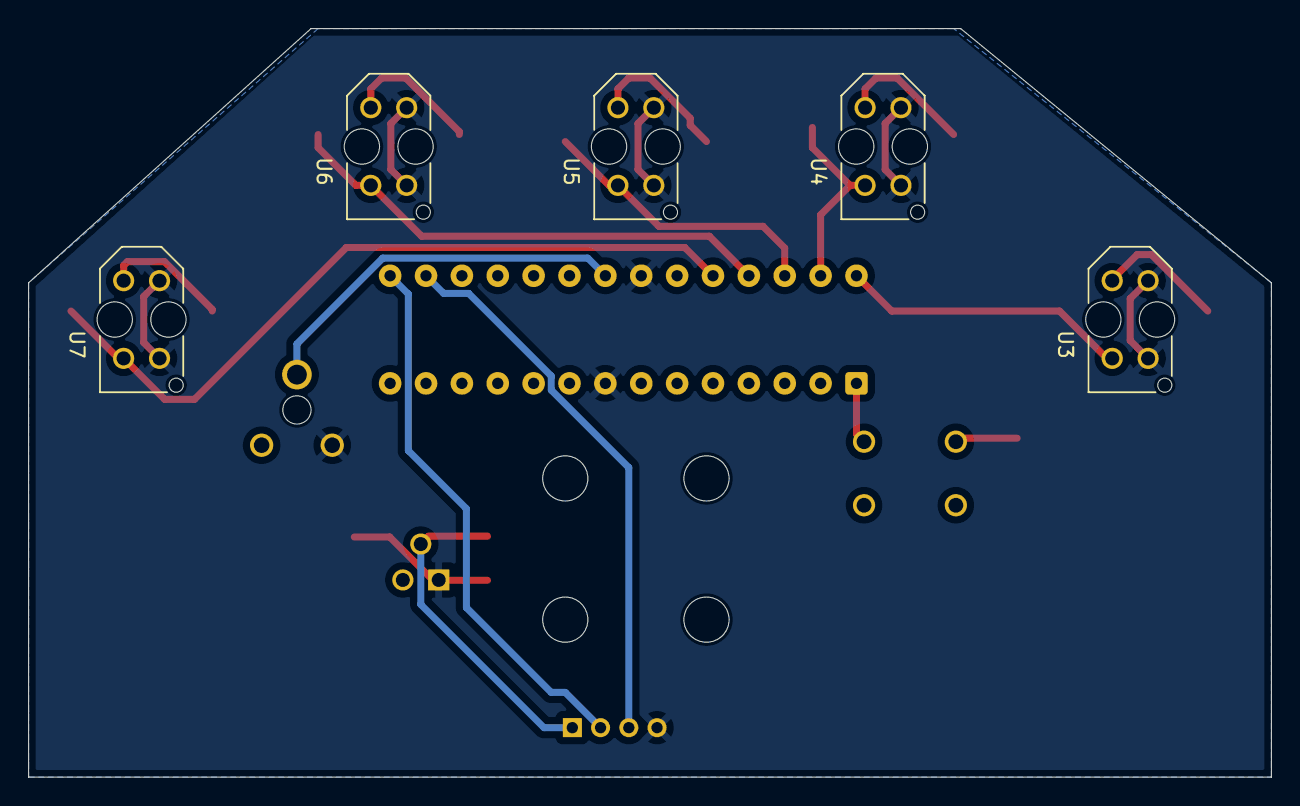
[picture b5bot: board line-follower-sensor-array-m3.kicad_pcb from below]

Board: 2 copper layers, 88.0 x 53.0 mm, 27 parts (5 on the bottom side), 18 nets.

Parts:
C1, C2: C; C_1206_3216Metric_Pad1.33x1.80mm_HandSolder
H1, H2, H3, H4: MountingHole; MountingHole_3.2mm_M3
J1: Vin, PWM OUT; PinHeader_1x04_P2.00mm_Horizontal
R1, R2, R3, R4, R5: 470; R_0805_2012Metric_Pad1.20x1.40mm_HandSolder
R6, R7, R8, R9, R10: 100k; R_0805_2012Metric_Pad1.20x1.40mm_HandSolder
R11: 10k; R_0805_2012Metric_Pad1.20x1.40mm_HandSolder
R12: N6-L50T0C-103; TRIM_N6-L50T0C-103
SW1: SW_Push_Open; MJTP1230
U1: MCP1700-3302E_TO; TO127P254X495-3
U2: ATmega328-P; DIP-28_W7.62mm
U3, U4, U5, U6, U7: TCRT5000; OPTO_TCRT5000

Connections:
GND: C1.2, C2.2, J1.4, R12.A, U1.1 (GND), U2.8 (GND), U2.22 (GND), U3.CATH, U3.E, U4.CATH, U4.E, U5.CATH, U5.E, U6.CATH, U6.E, U7.CATH, U7.E
Motor1: J1.2, U2.15 (PB1)
Motor2: J1.3, U2.16 (PB2)
unnamed: R1.2, U3.A
unnamed: R2.2, U4.A
unnamed: R3.2, U5.A
unnamed: R4.2, U6.A
unnamed: R5.2, U7.A
unnamed: SW1.1 (A), U2.1 (~RESET/PC6)
unnamed: R11.2, SW1.2 (B)
unnamed: R12.S, U2.21 (AREF)
unnamed: R10.2, U2.24 (PC1), U7.COLL
unnamed: R9.2, U2.25 (PC2), U6.COLL
unnamed: R8.2, U2.26 (PC3), U5.COLL
unnamed: R7.2, U2.27 (PC4), U4.COLL
unnamed: R6.2, U2.28 (PC5), U3.COLL
Vcc: C2.1, R1.1, R2.1, R3.1, R4.1, R5.1, R6.1, R7.1, R8.1, R9.1, R10.1, R11.1, R12.E, U1.3 (VOUT), U2.7 (VCC), U2.20 (AVCC)
Vdd: C1.1, J1.1, U1.2 (VIN)

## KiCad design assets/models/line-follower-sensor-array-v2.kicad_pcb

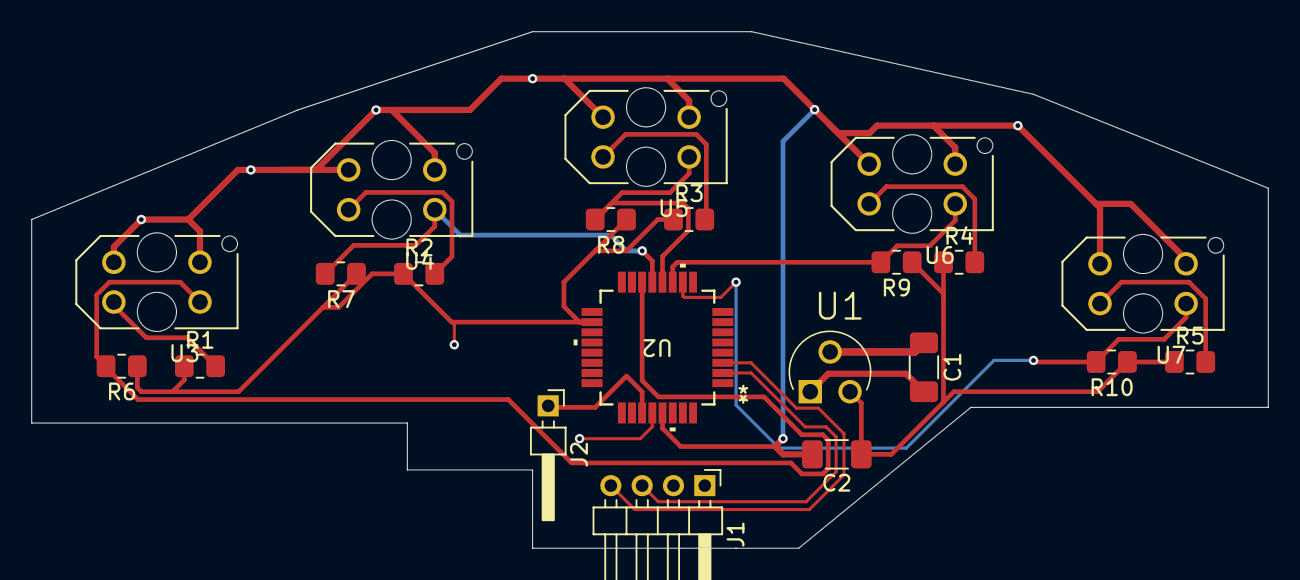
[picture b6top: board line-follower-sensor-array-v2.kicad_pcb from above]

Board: 4 copper layers, 79.0 x 33.0 mm, 21 parts (0 on the bottom side), 16 nets.

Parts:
C1, C2: C; C_1206_3216Metric_Pad1.33x1.80mm_HandSolder
J1: Vin, PWM OUT; PinHeader_1x04_P2.00mm_Horizontal
J2: Programming Pin; PinHeader_1x01_P2.00mm_Horizontal
R1, R2, R3, R4, R5: 470; R_0805_2012Metric_Pad1.20x1.40mm_HandSolder
R6, R7, R8, R9, R10: 100k; R_0805_2012Metric_Pad1.20x1.40mm_HandSolder
U1: MCP1700-3302E_TO; TO127P254X495-3
U2: ATMEGA4808-AFR; TQFP32_PT_MCH
U3, U4, U5, U6, U7: TCRT5000; OPTO_TCRT5000

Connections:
GND: C1.2, C2.2, J1.2, U1.1 (GND), U2.29 (GND), U3.CATH, U3.E, U4.CATH, U4.E, U5.CATH, U5.E, U6.CATH, U6.E, U7.CATH, U7.E
unnamed: J1.3, U2.2 (PA4)
unnamed: J1.4, U2.3 (PA5)
unnamed: J2.1, U2.27 (UPDI)
unnamed: R1.2, U3.A
unnamed: R2.2, U4.A
unnamed: R3.2, U5.A
unnamed: R4.2, U6.A
unnamed: R5.2, U7.A
unnamed: R10.2, U2.10 (PD0), U7.COLL
unnamed: R9.2, U2.11 (PD1), U6.COLL
unnamed: R8.2, U2.12 (PD2), U5.COLL
unnamed: R7.2, U2.13 (PD3), U4.COLL
unnamed: R6.2, U2.14 (PD4), U3.COLL
Vcc: C2.1, R1.1, R2.1, R3.1, R4.1, R5.1, R6.1, R7.1, R8.1, R9.1, R10.1, U1.3 (VOUT), U2.18 (AVDD), U2.28 (VDD)
Vdd: C1.1, J1.1, U1.2 (VIN)
